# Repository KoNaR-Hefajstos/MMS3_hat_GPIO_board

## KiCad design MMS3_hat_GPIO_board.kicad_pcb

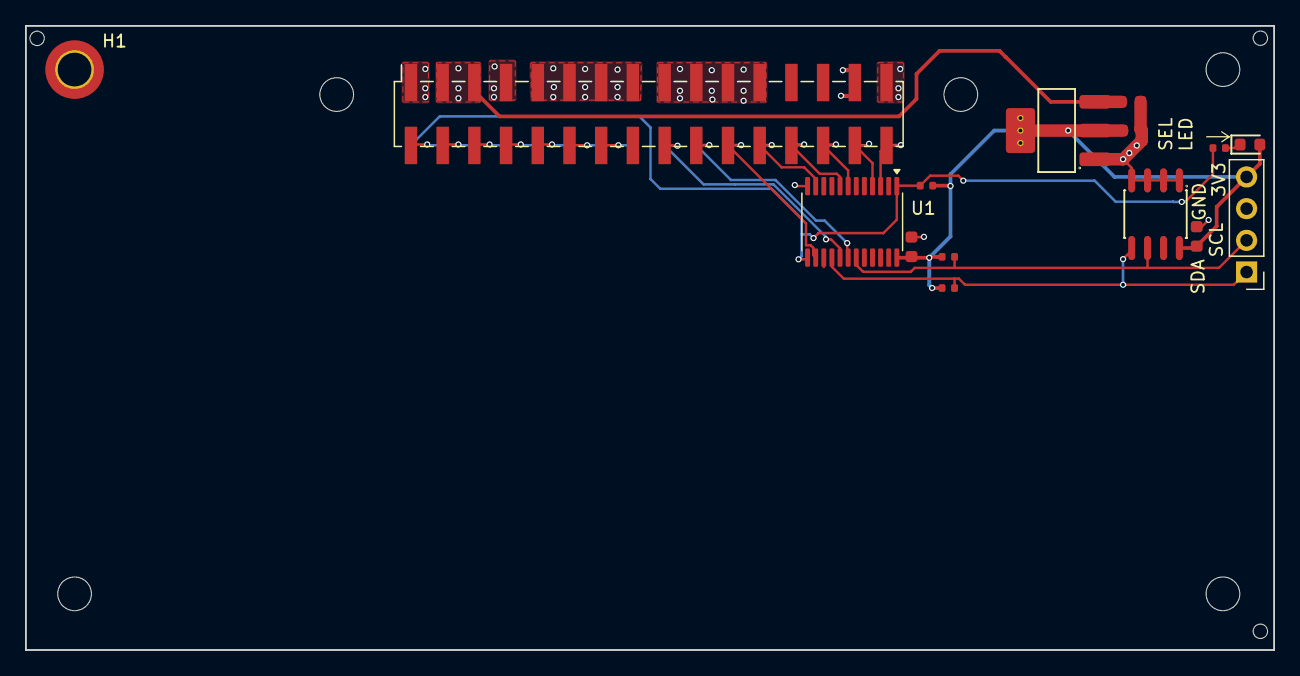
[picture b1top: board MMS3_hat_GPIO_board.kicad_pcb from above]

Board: 2 copper layers, 100.0 x 50.0 mm, 24 parts (1 on the bottom side), 24 nets.

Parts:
C1, C2: 100nF; C_0603
C16, C18: 10uF; C_0603
D3: Red; D_0603
H1: M2.5 Mount; MountingHole_2.7mm_M2.5_DIN965_Pad_TopOnly
H2, H3, H4, H5, H6: M2.5 mount; MountingHole_2.7mm_M2.5
H7, H8, H9: Hole_Tooling_JLCPCB
J1: Chainbus in; PinHeader_2x16_P2.54mm_Vertical_SMD
J2: Chainbus Out; PinSocket_2x16_P2.54mm_Vertical_SMD
J3: Conn_01x04_Pin; PinHeader_1x04_P2.54mm_Vertical
R1: 330Ω; R_0402
R4, R6, R10: 10kΩ; R_0402
U1: SN74CB3Q3384APW; TSSOP-24_4.4x7.8mm_P0.65mm
U2: M24C64; SOIC-8_L5.0-W4.0-P1.27-LS6.0-BL
U4: AMS1117; SOT-223-3_L6.5-W3.4-P2.30-LS7.0-BR

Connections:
+3V3: C1.1, C2.1, C18.1, D3.2, J3.4, R4.2, R6.1, R10.1, U1.24 (VCC), U2.8 (VCC), U4.2 (VOUT), U4.4 (VOUT)
+5V: C16.1, J1.3, J1.5, J2.3, J2.5, U4.3 (VIN)
+12V stby: J1.29, J2.29
/Bus_switch/Chainbus.SCL: J3.2, R6.2, U1.19 (2B3), U2.6 (SCL)
/Bus_switch/Chainbus.SDA: J3.1, R10.2, U1.16 (2B2), U2.5 (SDA)
/Bus_switch/Chainbus_In.CS: J1.22, J2.22, U1.14 (2A1)
/Bus_switch/Chainbus_In.MISO: J1.28, J2.28, U1.7 (1A3)
/Bus_switch/Chainbus_In.MOSI: J1.26, J2.26, U1.8 (1A4)
/Bus_switch/Chainbus_In.RX: J1.32, J2.32, U1.3 (1A1)
/Bus_switch/Chainbus_In.SCK: J1.24, J2.24, U1.11 (1A5)
/Bus_switch/Chainbus_In.SCL: J1.20, J2.20, U1.18 (2A3)
/Bus_switch/Chainbus_In.SDA: J1.18, J2.18, U1.17 (2A2)
/Bus_switch/Chainbus_In.TX: J1.30, J2.30, U1.4 (1A2)
/Bus_switch/SEL1: J1.2, R1.1, R4.1, U1.1 (~1OE), U1.13 (~2OE)
/Interboard_connector/SEL2: J1.4, J2.2
/Interboard_connector/SEL3: J1.6, J2.4
/Interboard_connector/SEL4: J1.8, J2.6
/Interboard_connector/SEL5: J1.10, J2.8
/Interboard_connector/SEL6: J1.12, J2.10
/Interboard_connector/SEL7: J1.14, J2.12
/Interboard_connector/SEL8: J1.16, J2.14
GND: C1.2, C2.2, C16.2, C18.2, H1.1 (1_1), J1.1, J1.7, J1.17, J1.19, J1.21, J1.23, J1.31, J2.1, J2.7, J2.17, J2.19, J2.21, J2.23, J2.31, J3.3, U1.12 (GND), U2.1 (A0), U2.2 (A1), U2.3 (A2), U2.4 (VSS), U4.1 (GND)
unnamed: D3.1, R1.2
VIN_CHAINBUS: J1.9, J1.11, J1.13, J1.15, J2.9, J2.11, J2.13, J2.15

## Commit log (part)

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2026-06-09 temp commit
2026-06-23 routing impossible
